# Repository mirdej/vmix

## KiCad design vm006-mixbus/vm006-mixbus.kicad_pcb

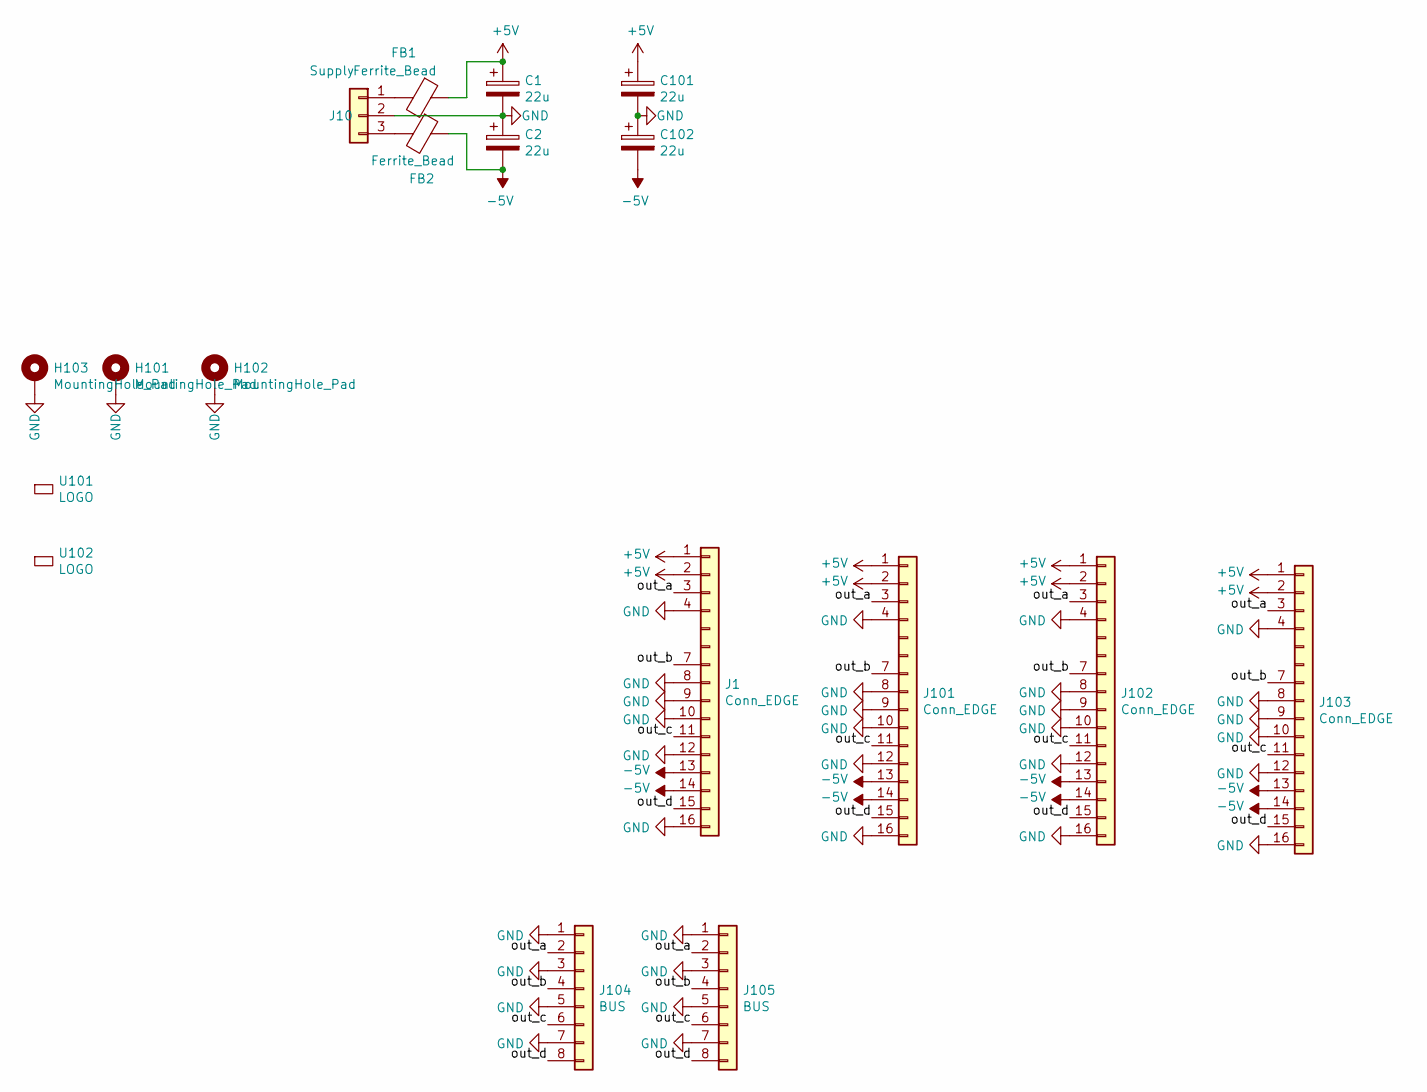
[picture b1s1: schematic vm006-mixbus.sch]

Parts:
C1, C2, C101, C102: 22u; CP_EIA-7360-38_Kemet-E_Pad2.25x4.25mm_HandSolder
FB1, FB2: Ferrite_Bead; L_1206_3216Metric_Pad1.42x1.75mm_HandSolder
H101, H102, H103: MountingHole_Pad; MountingHole_3.2mm_M3_Pad
J1, J101, J102, J103: Conn_EDGE; Samtec_MECF-08-01-L-DV-WT_2x08_P1.27mm_Polarized_Socket_Hor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
J10: Supply; Molex_KK-254_AE-6410-03A_1x03_P2.54mm_Vertical
J104, J105: BUS; PinHeader_1x08_P2.54mm_Vertical
U101: LOGO; logo_anyma
U102: LOGO; OSHW-Logo2_9.8x8mm_SilkScreen

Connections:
+5V: C1.1, C101.1, FB1.1, J1.1, J1.2, J101.1, J101.2, J102.1, J102.2, J103.1, J103.2
-5V: C2.2, C102.2, FB2.1, J1.13, J1.14, J101.13, J101.14, J102.13, J102.14, J103.13, J103.14
/out_a: J1.3, J101.3, J102.3, J103.3, J104.2, J105.2
/out_b: J1.7, J101.7, J102.7, J103.7, J104.4, J105.4
/out_c: J1.11, J101.11, J102.11, J103.11, J104.6, J105.6
/out_d: J1.15, J101.15, J102.15, J103.15, J104.8, J105.8
GND: C1.2, C2.1, C101.2, C102.1, H101.1, H102.1, H103.1, J1.4, J1.8, J1.9, J1.10, J1.12, J1.16, J10.2, J101.4, J101.8, J101.9, J101.10, J101.12, J101.16, J102.4, J102.8, J102.9, J102.10, J102.12, J102.16, J103.4, J103.8, J103.9, J103.10, J103.12, J103.16, J104.1, J104.3, J104.5, J104.7, J105.1, J105.3, J105.5, J105.7
unnamed: FB1.2, J10.1
unnamed: FB2.2, J10.3

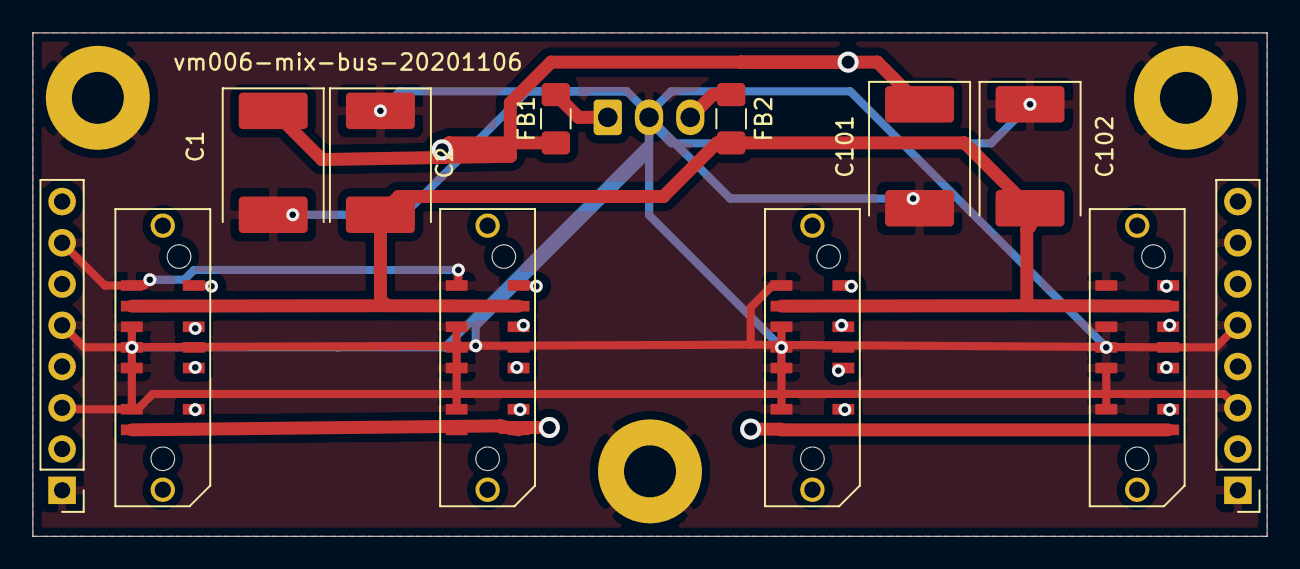
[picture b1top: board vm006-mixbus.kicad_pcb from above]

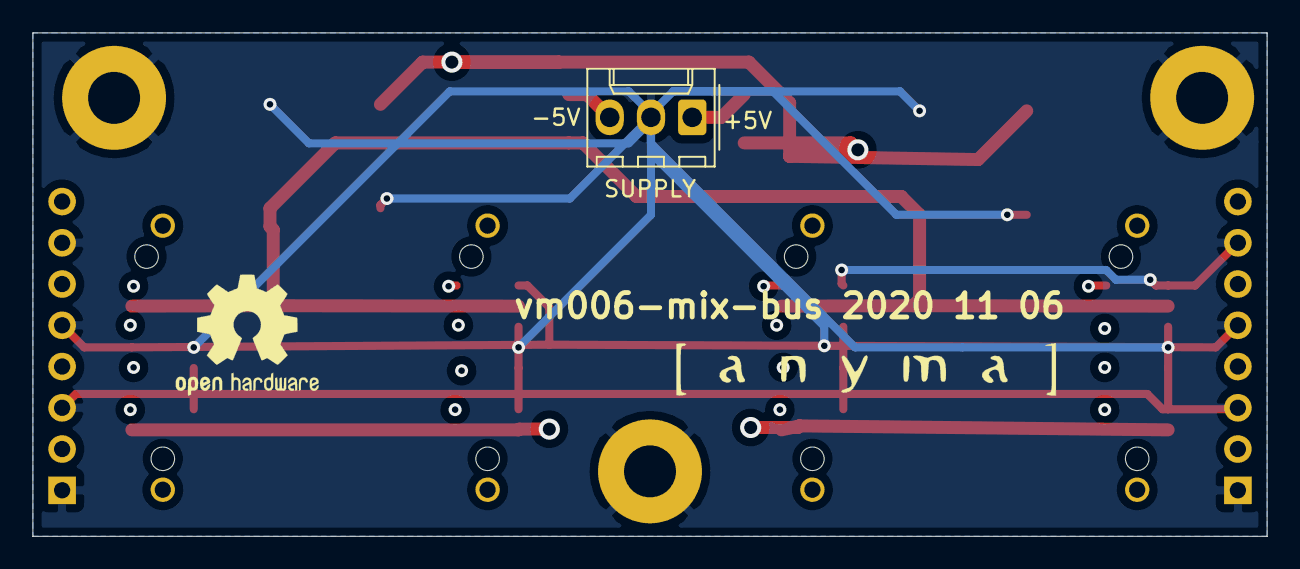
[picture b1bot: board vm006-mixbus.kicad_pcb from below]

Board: 4 copper layers, 76.0 x 31.0 mm, 18 parts (3 on the bottom side), 9 nets.

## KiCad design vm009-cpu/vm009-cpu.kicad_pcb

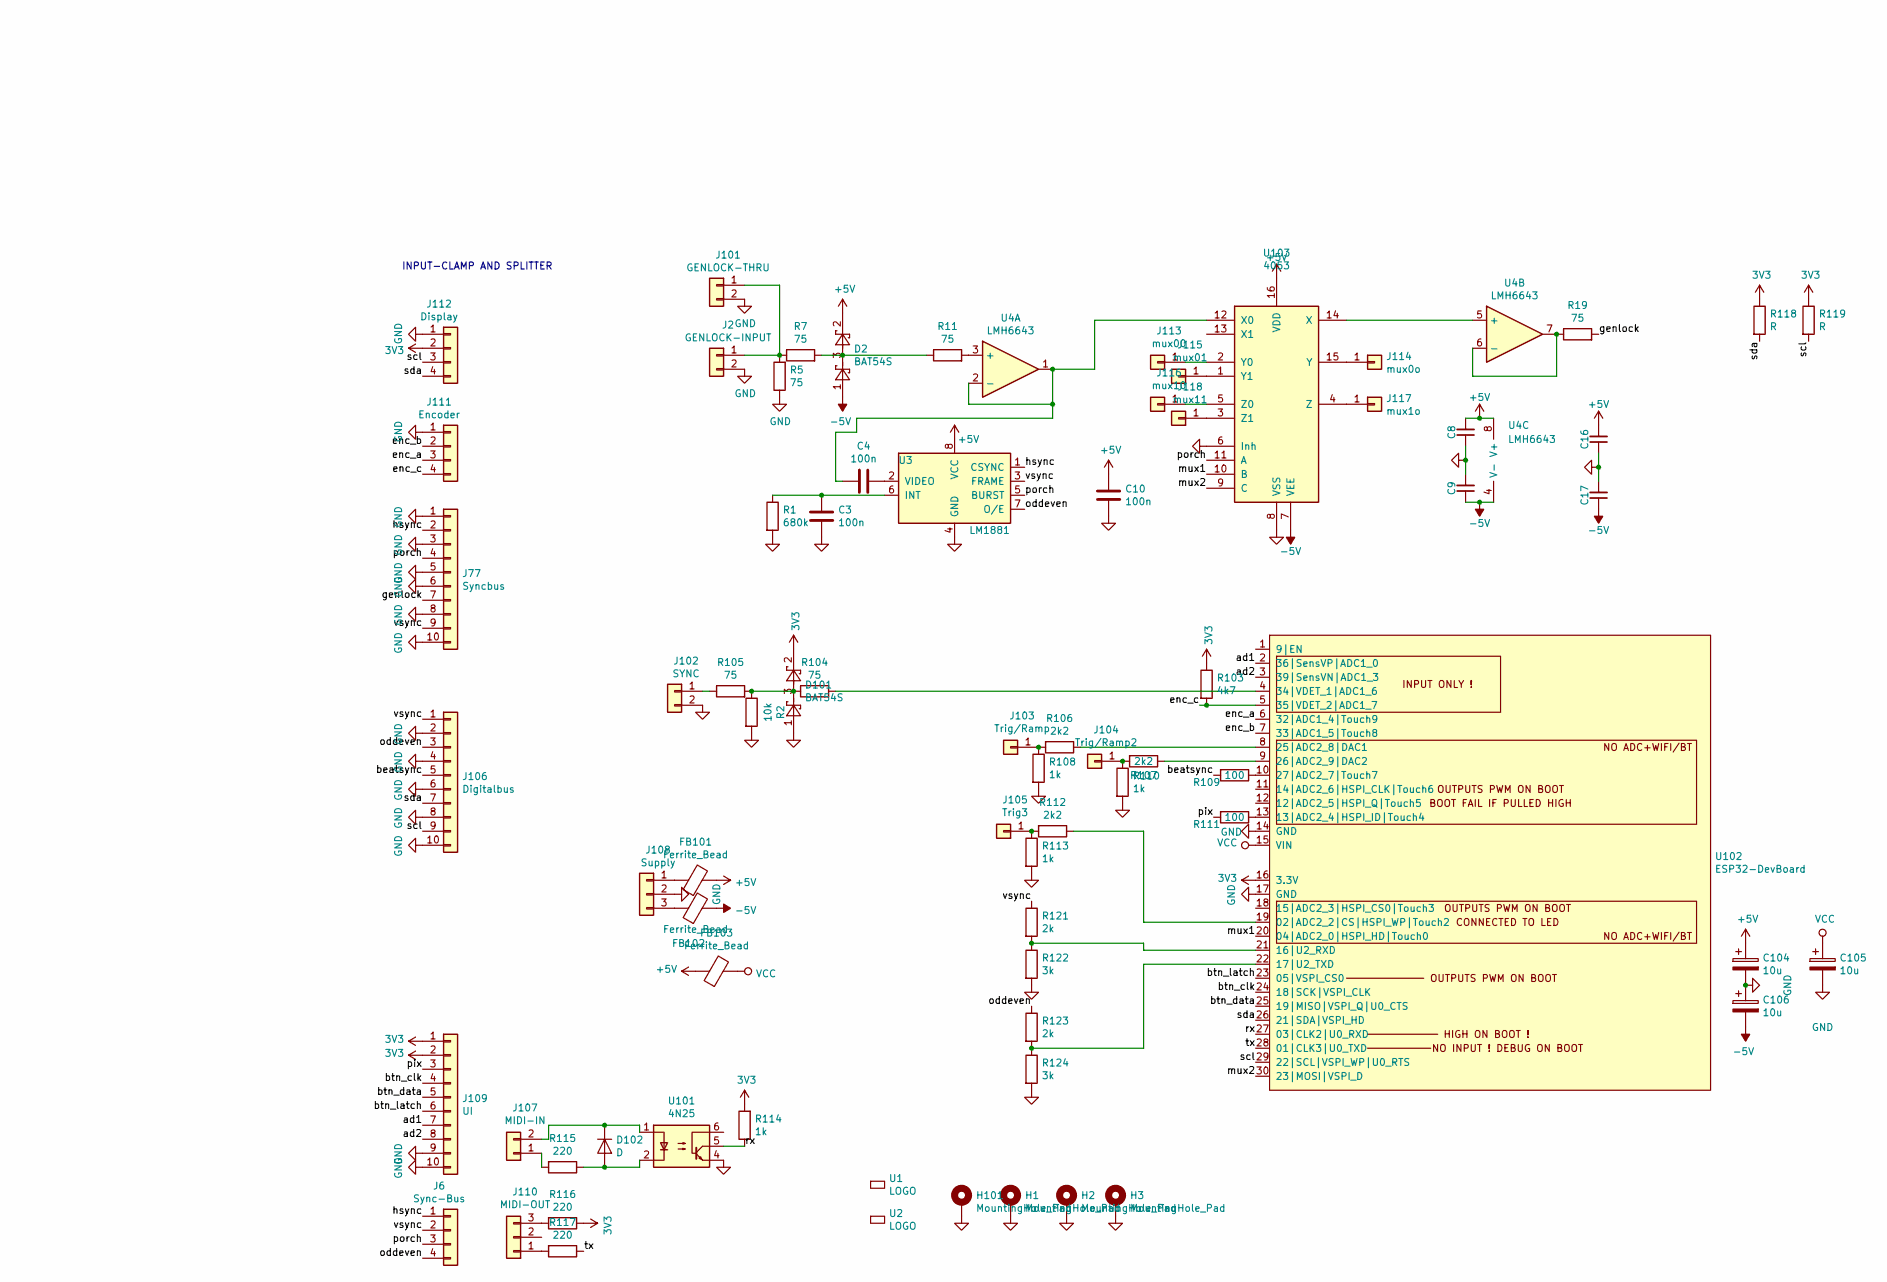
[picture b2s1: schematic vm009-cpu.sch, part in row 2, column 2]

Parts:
C3, C4, C8, C9, C10, C16, C17: 100n; C_0603_1608Metric_Pad1.05x0.95mm_HandSolder
C104, C105, C106: 10u; CP_EIA-3528-21_Kemet-B_Pad1.50x2.35mm_HandSolder
D2, D101: BAT54S; SOT-23
D102: D; D_MiniMELF_Handsoldering
FB101, FB102, FB103: Ferrite_Bead; L_0805_2012Metric_Pad1.15x1.40mm_HandSolder
H1, H2, H3, H101: MountingHole_Pad; MountingHole_2.7mm_M2.5_ISO7380_Pad
J2: GENLOCK-INPUT; Molex_KK-254_AE-6410-02A_1x02_P2.54mm_Vertical
J6: Sync-Bus; Molex_KK-254_AE-6410-04A_1x04_P2.54mm_Vertical
J77: Syncbus; IDC-Header_2x05_P2.54mm_Vertical
J101: GENLOCK-THRU; Molex_KK-254_AE-6410-02A_1x02_P2.54mm_Vertical
J102: SYNC; Molex_KK-254_AE-6410-02A_1x02_P2.54mm_Vertical
J103: Trig/Ramp; Solderpad_1mm
J104: Trig/Ramp2; Solderpad_1mm
J105: Trig3; Solderpad_1mm
J106: Digitalbus; IDC-Header_2x05_P2.54mm_Vertical
J107: MIDI-IN; Molex_KK-254_AE-6410-02A_1x02_P2.54mm_Vertical
J108: Supply; Molex_KK-254_AE-6410-03A_1x03_P2.54mm_Vertical
J109: UI; IDC-Header_2x05_P2.54mm_Vertical
J110: MIDI-OUT; Molex_KK-254_AE-6410-03A_1x03_P2.54mm_Vertical
J111: Encoder; Molex_KK-254_AE-6410-04A_1x04_P2.54mm_Vertical
J112: Display; Molex_KK-254_AE-6410-04A_1x04_P2.54mm_Vertical
J113: mux00; Solderpad_1mm
J114: mux0o; Solderpad_1mm
J115: mux01; Solderpad_1mm
J116: mux10; Solderpad_1mm
J117: mux1o; Solderpad_1mm
J118: mux11; Solderpad_1mm
R1: 680k; R_0805_2012Metric_Pad1.15x1.40mm_HandSolder
R2: 10k; R_0805_2012Metric_Pad1.15x1.40mm_HandSolder
R5, R7, R11, R19, R104, R105: 75; R_0805_2012Metric_Pad1.15x1.40mm_HandSolder
R103: 4k7; R_0805_2012Metric_Pad1.15x1.40mm_HandSolder
R106, R107, R112: 2k2; R_0805_2012Metric_Pad1.15x1.40mm_HandSolder
R108, R110, R113, R114: 1k; R_0805_2012Metric_Pad1.15x1.40mm_HandSolder
R109, R111: 100; R_0805_2012Metric_Pad1.15x1.40mm_HandSolder
R115, R116, R117: 220; R_0805_2012Metric_Pad1.15x1.40mm_HandSolder
R118, R119: R; R_0805_2012Metric_Pad1.15x1.40mm_HandSolder
R121, R123: 2k; R_0805_2012Metric_Pad1.15x1.40mm_HandSolder
R122, R124: 3k; R_0805_2012Metric_Pad1.15x1.40mm_HandSolder
U1: LOGO; logo_anyma
U2: LOGO; OSHW-Logo2_7.3x6mm_SilkScreen
U3: LM1881; SOIC-8_3.9x4.9mm_P1.27mm
U4: LMH6643; SOIC-8_3.9x4.9mm_P1.27mm
U101: 4N25; DIP-6_W8.89mm_SMDSocket_LongPads
U102: ESP32-DevBoard; ESP32_Devboard
U103: 4053; SOIC-16_3.9x9.9mm_P1.27mm

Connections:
3V3: D101.2, J109.1, J109.2, J112.2, R103.1, R114.2, R116.1, R118.1, R119.1, U102.16 (3.3V)
+5V: C8.2, C10.1, C16.2, C104.1, D2.2, FB101.2, FB103.1, U3.8 (VCC), U4.8 (V+), U103.16 (VDD)
-5V: C9.1, C17.1, C106.2, D2.1, FB102.2, U4.4 (V-), U103.7 (VEE)
/ad1: J109.7, U102.2 (36|SensVP|ADC1_0)
/ad2: J109.8, U102.3 (39|SensVN|ADC1_3)
/beatsync: J106.5, R109.2
/btn_clk: J109.4, U102.24 (18|SCK|VSPI_CLK)
/btn_data: J109.5, U102.25 (19|MISO|VSPI_Q|U0_CTS)
/btn_latch: J109.6, U102.23 (05|VSPI_CS0)
/enc_a: J111.3, U102.6 (32|ADC1_4|Touch9)
/enc_b: J111.2, U102.7 (33|ADC1_5|Touch8)
/enc_c: J111.4, R103.2, U102.5 (35|VDET_2|ADC1_7)
/genlock: J77.7, R19.2
/hsync: J6.1, J77.2, U3.1 (CSYNC)
/mux1: U102.20 (04|ADC2_0|HSPI_HD|Touch0), U103.10 (B)
/mux2: U102.30 (23|MOSI|VSPI_D), U103.9 (C)
/oddeven: J6.4, J106.3, R123.1, U3.7 (O/E)
/pix: J109.3, R111.2
/porch: J6.3, J77.4, U3.5 (BURST), U103.11 (A)
/rx: R114.1, U101.5, U102.27 (03|CLK2|U0_RXD)
/scl: J106.9, J112.3, R119.2, U102.29 (22|SCL|VSPI_WP|U0_RTS)
/sda: J106.7, J112.4, R118.2, U102.26 (21|SDA|VSPI_HD)
/tx: R117.1, U102.28 (01|CLK3|U0_TXD)
/vsync: J6.2, J77.9, J106.1, R121.1, U3.3 (FRAME)
GND: C3.2, C8.1, C9.2, C10.2, C16.1, C17.2, C104.2, C105.2, C106.1, D101.1, H1.1, H2.1, H3.1, H101.1, J2.2, J77.1, J77.3, J77.5, J77.6, J77.8, J77.10, J101.2, J102.2, J106.2, J106.4, J106.6, J106.8, J106.10, J108.2, J109.9, J109.10, J111.1, J112.1, R1.2, R2.2, R5.1, R108.2, R110.2, R113.2, R122.2, R124.2, U3.4 (GND), U101.4, U102.14 (GND), U102.17 (GND), U103.6 (Inh), U103.8 (VSS)
unnamed: C3.1, R1.1, U3.6 (INT)
unnamed: C4.1, U3.2 (VIDEO)
unnamed: C4.2, U4.1, U4.2 (-), U103.12 (X0)
unnamed: D2.3, R7.2, R11.1
unnamed: D101.3, R2.1, R104.1, R105.2
unnamed: D102.1 (K), J107.2, U101.1
unnamed: D102.2 (A), R115.1, U101.2
unnamed: FB101.1, J108.1
unnamed: FB102.1, J108.3
unnamed: J2.1, J101.1, R5.2, R7.1
unnamed: J102.1, R105.1
unnamed: J103.1, R106.2, R108.1
unnamed: J104.1, R107.2, R110.1
unnamed: J105.1, R112.2, R113.1
unnamed: J107.1, R115.2
unnamed: J110.1, R117.2
unnamed: J110.3, R116.2
unnamed: J113.1, U103.2 (Y0)
unnamed: J114.1, U103.15 (Y)
unnamed: J115.1, U103.1 (Y1)
unnamed: J116.1, U103.5 (Z0)
unnamed: J117.1, U103.4 (Z)
unnamed: J118.1, U103.3 (Z1)
unnamed: R11.2, U4.3 (+)
unnamed: R19.1, U4.6 (-), U4.7
unnamed: R104.2, U102.4 (34|VDET_1|ADC1_6)
unnamed: R106.1, U102.8 (25|ADC2_8|DAC1)
unnamed: R107.1, U102.9 (26|ADC2_9|DAC2)
unnamed: R109.1, U102.10 (27|ADC2_7|Touch7)
unnamed: R111.1, U102.13 (13|ADC2_4|HSPI_ID|Touch4)
unnamed: R112.1, U102.19 (02|ADC2_2|CS|HSPI_WP|Touch2)
unnamed: R121.2, R122.1, U102.21 (16|U2_RXD)
unnamed: R123.2, R124.1, U102.22 (17|U2_TXD)
unnamed: U4.5 (+), U103.14 (X)
VCC: C105.1, FB103.2, U102.15 (VIN)

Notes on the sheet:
INPUT-CLAMP AND SPLITTER

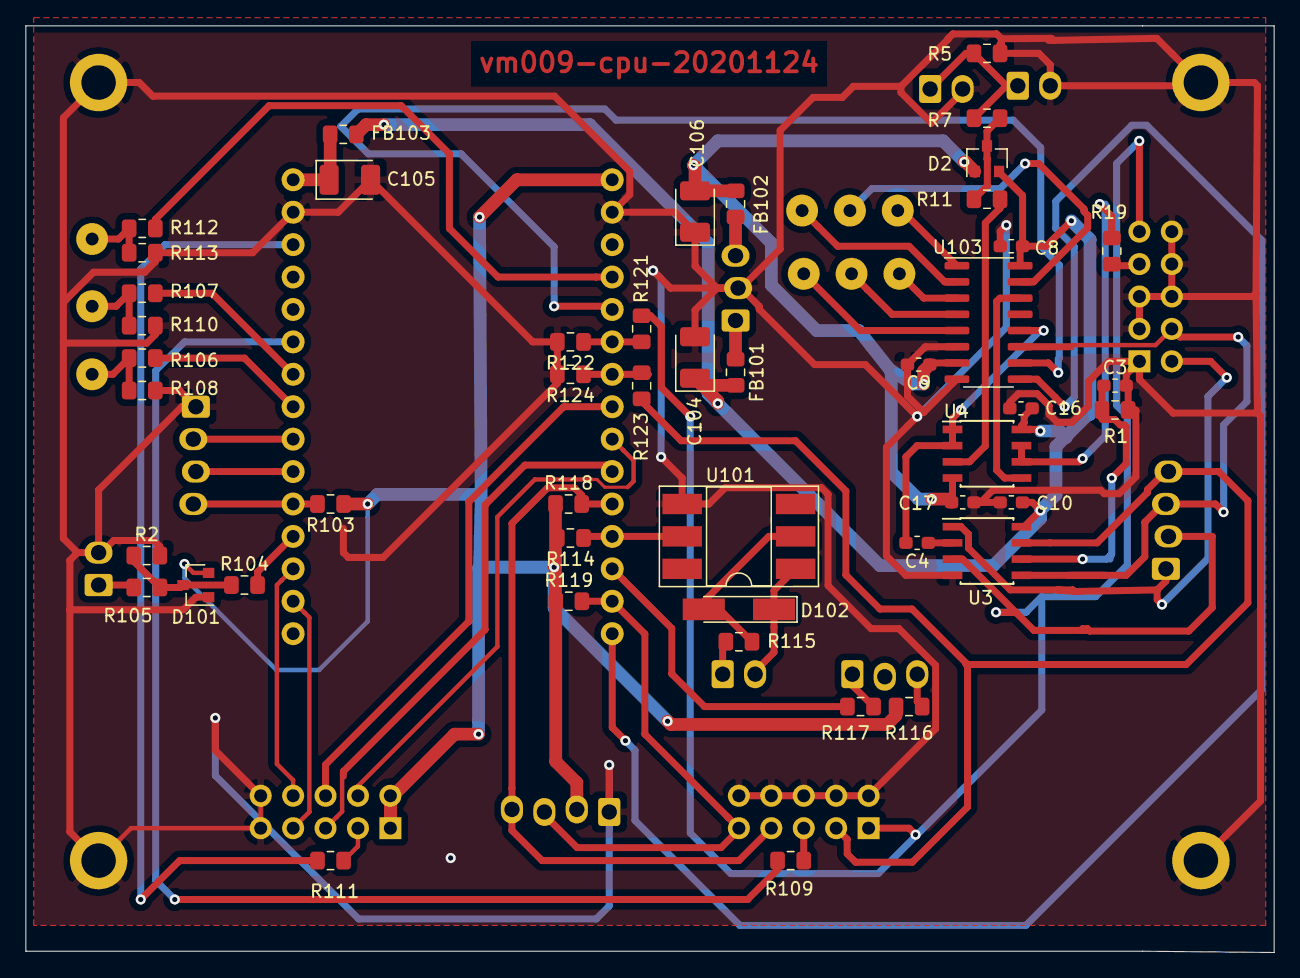
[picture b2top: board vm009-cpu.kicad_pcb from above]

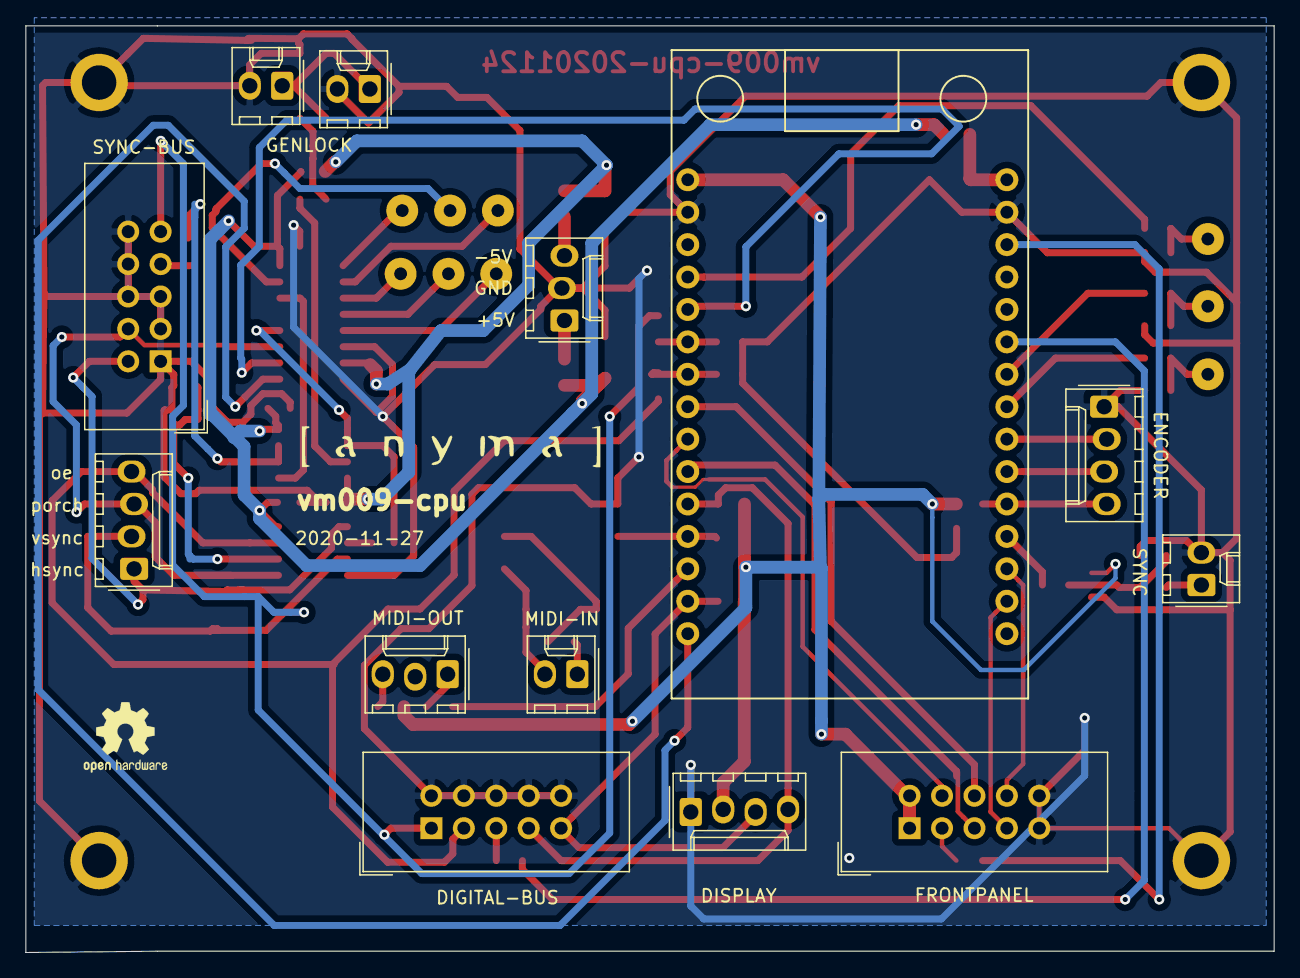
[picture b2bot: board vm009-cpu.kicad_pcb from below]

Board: 2 copper layers, 97.8 x 72.6 mm, 75 parts (15 on the bottom side), 60 nets.

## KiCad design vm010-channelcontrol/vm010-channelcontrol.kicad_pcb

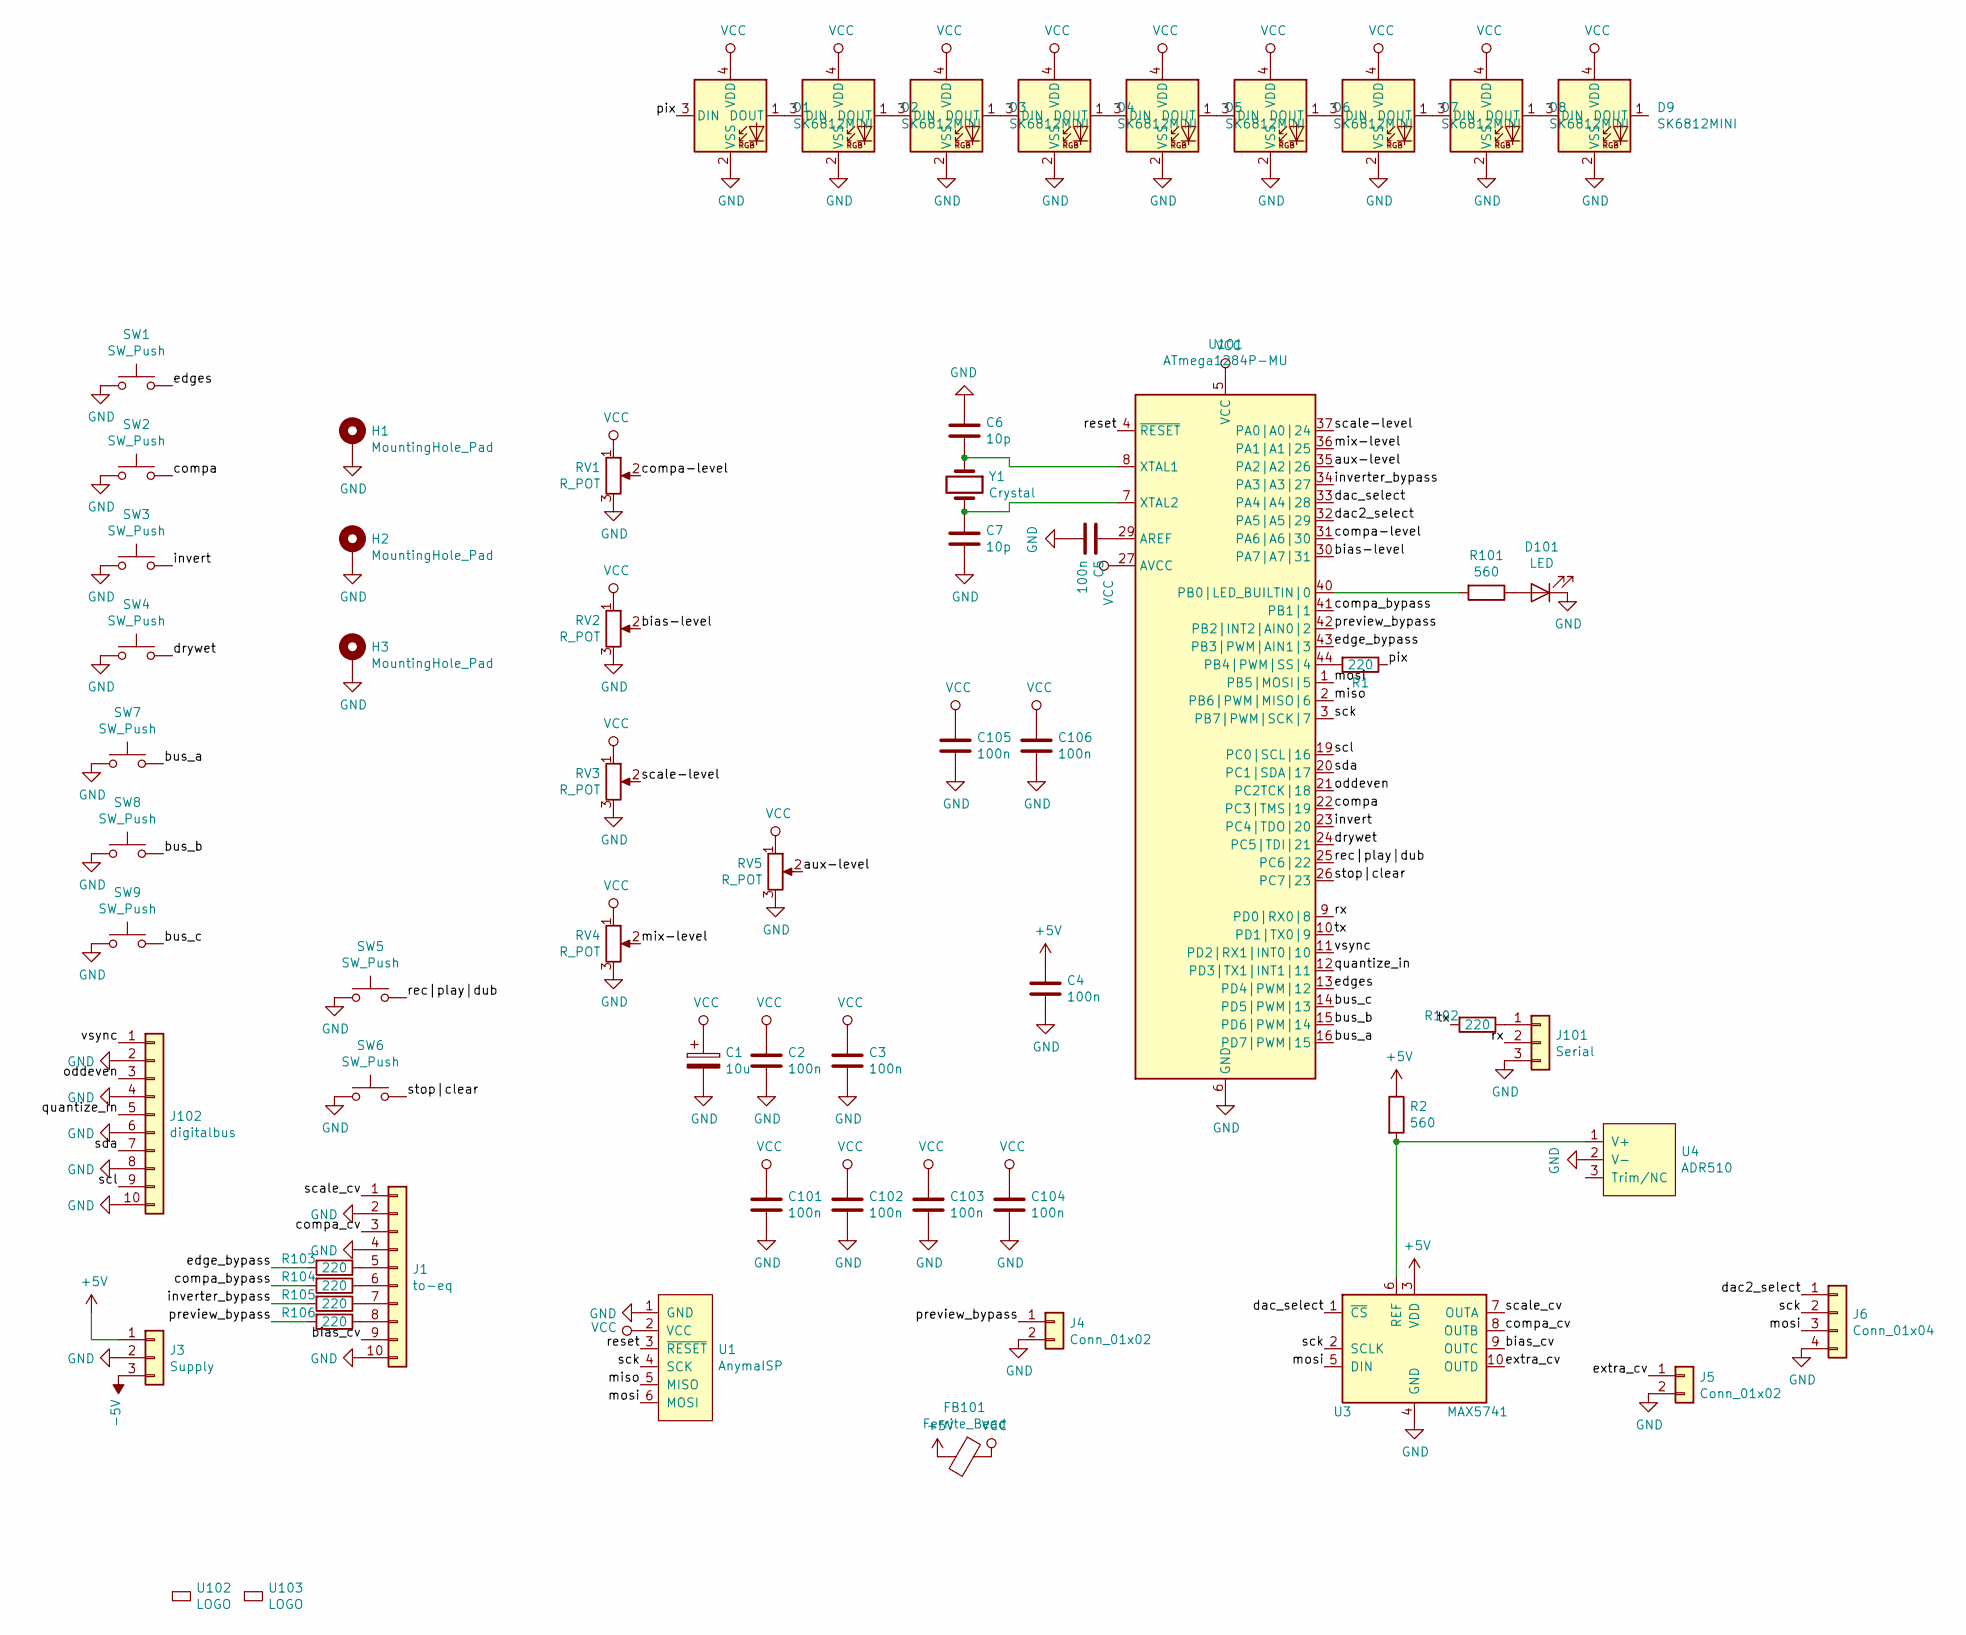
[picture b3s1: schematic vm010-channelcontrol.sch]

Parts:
C1: 10u; CP_EIA-3528-21_Kemet-B_Pad1.50x2.35mm_HandSolder
C2, C3, C4, C5, C101, C102, C103, C104, C105, C106: 100n; R_0603_1608Metric_Pad1.05x0.95mm_HandSolder
C6, C7: 10p; R_0805_2012Metric_Pad1.15x1.40mm_HandSolder
D1, D2, D3, D4, D5, D6, D7, D8, D9: SK6812MINI; LED_SK6812MINI_PLCC4_3.5x3.5mm_P1.75mm
D101: LED; LED_0805_2012Metric
FB101: Ferrite_Bead; L_0805_2012Metric_Pad1.15x1.40mm_HandSolder
H1, H2, H3: MountingHole_Pad; MountingHole_2.2mm_M2_DIN965_Pad
J1: to-eq; IDC-Header_2x05_P2.54mm_Vertical
J3: Supply; Molex_KK-254_AE-6410-03A_1x03_P2.54mm_Vertical
J4, J5: Conn_01x02; Molex_KK-254_AE-6410-02A_1x02_P2.54mm_Vertical
J6: Conn_01x04; Molex_KK-254_AE-6410-04A_1x04_P2.54mm_Vertical
J101: Serial; Molex_KK-254_AE-6410-03A_1x03_P2.54mm_Vertical
J102: digitalbus; IDC-Header_2x05_P2.54mm_Vertical
R1, R102, R103, R104, R105, R106: 220; R_0805_2012Metric_Pad1.15x1.40mm_HandSolder
R2, R101: 560; R_0805_2012Metric_Pad1.15x1.40mm_HandSolder
RV1, RV2, RV3, RV5: R_POT; Potentiometer_Alps_RK09K_Single_Vertical
RV4: R_POT; Potentiometer_Alps_RS6011xP_Slide
SW1, SW2, SW3, SW4, SW5, SW6, SW7, SW8, SW9: SW_Push; Alps_Tactile_Switch
U1: AnymaISP; PinHeader_1x06_P2.54mm_Vertical
U3: MAX5741; MSOP-10_3x3mm_P0.5mm
U4: ADR510; SOT-23
U101: ATmega1284P-MU; QFN-44-1EP_7x7mm_P0.5mm_EP5.2x5.2mm
U102: LOGO; logo_anyma
U103: LOGO; OSHW-Logo2_7.3x6mm_SilkScreen
Y1: Crystal; Crystal_SMD_HC49-SD

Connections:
+5V: C4.1, FB101.2, J3.1, R2.1, U3.3 (VDD)
/aux-level: RV5.2, U101.35 (PA2|A2|26)
/bias-level: RV2.2, U101.30 (PA7|A7|31)
/bias_cv: J1.9, U3.9 (OUTC)
/bus_a: SW7.2, U101.16 (PD7|PWM|15)
/bus_b: SW8.2, U101.15 (PD6|PWM|14)
/bus_c: SW9.2, U101.14 (PD5|PWM|13)
/compa: SW2.2, U101.22 (PC3|TMS|19)
/compa-level: RV1.2, U101.31 (PA6|A6|30)
/compa_bypass: R104.2, U101.41 (PB1|1)
/compa_cv: J1.3, U3.8 (OUTB)
/dac2_select: J6.1, U101.32 (PA5|A5|29)
/dac_select: U3.1 (~CS~), U101.33 (PA4|A4|28)
/drywet: SW4.2, U101.24 (PC5|TDI|21)
/edge_bypass: R103.2, U101.43 (PB3|PWM|AIN1|3)
/edges: SW1.2, U101.13 (PD4|PWM|12)
/extra_cv: J5.1, U3.10 (OUTD)
/invert: SW3.2, U101.23 (PC4|TDO|20)
/inverter_bypass: R105.2, U101.34 (PA3|A3|27)
/miso: U1.5 (MISO), U101.2 (PB6|PWM|MISO|6)
/mix-level: RV4.2, U101.36 (PA1|A1|25)
/mosi: J6.3, U1.6 (MOSI), U3.5 (DIN), U101.1 (PB5|MOSI|5)
/oddeven: J102.3, U101.21 (PC2TCK|18)
/pix: D1.3 (DIN), R1.1
/preview_bypass: J4.1, R106.2, U101.42 (PB2|INT2|AIN0|2)
/quantize_in: J102.5, U101.12 (PD3|TX1|INT1|11)
/rec|play|dub: SW5.2, U101.25 (PC6|22)
/reset: U1.3 (~RESET), U101.4 (~RESET)
/rx: J101.2, U101.9 (PD0|RX0|8)
/scale-level: RV3.2, U101.37 (PA0|A0|24)
/scale_cv: J1.1, U3.7 (OUTA)
/sck: J6.2, U1.4 (SCK), U3.2 (SCLK), U101.3 (PB7|PWM|SCK|7)
/scl: J102.9, U101.19 (PC0|SCL|16)
/sda: J102.7, U101.20 (PC1|SDA|17)
/stop|clear: SW6.2, U101.26 (PC7|23)
/tx: R102.2, U101.10 (PD1|TX0|9)
/vsync: J102.1, U101.11 (PD2|RX1|INT0|10)
GND: C1.2, C2.2, C3.2, C4.2, C5.2, C6.1, C7.2, C101.2, C102.2, C103.2, C104.2, C105.2, C106.2, D1.2 (VSS), D2.2 (VSS), D3.2 (VSS), D4.2 (VSS), D5.2 (VSS), D6.2 (VSS), D7.2 (VSS), D8.2 (VSS), D9.2 (VSS), D101.1 (K), H1.1, H2.1, H3.1, J1.2, J1.4, J1.10, J3.2, J4.2, J5.2, J6.4, J101.3, J102.2, J102.4, J102.6, J102.8, J102.10, RV1.3, RV2.3, RV3.3, RV4.3, RV5.3, SW1.1, SW2.1, SW3.1, SW4.1, SW5.1, SW6.1, SW7.1, SW8.1, SW9.1, U1.1 (GND), U3.4 (GND), U4.2 (V-), U101.6 (GND), U101.18 (GND), U101.28 (GND), U101.39 (GND), U101.45 (GND); also elsewhere on the board
unnamed: C5.1, U101.29 (AREF)
unnamed: C6.2, U101.8 (XTAL1), Y1.1
unnamed: C7.1, U101.7 (XTAL2), Y1.2
unnamed: D1.1 (DOUT), D2.3 (DIN)
unnamed: D2.1 (DOUT), D3.3 (DIN)
unnamed: D3.1 (DOUT), D4.3 (DIN)
unnamed: D4.1 (DOUT), D5.3 (DIN)
unnamed: D5.1 (DOUT), D6.3 (DIN)
unnamed: D6.1 (DOUT), D7.3 (DIN)
unnamed: D7.1 (DOUT), D8.3 (DIN)
unnamed: D8.1 (DOUT), D9.3 (DIN)
unnamed: D101.2 (A), R101.1
unnamed: J1.5, R103.1
unnamed: J1.6, R104.1
unnamed: J1.7, R105.1
unnamed: J1.8, R106.1
unnamed: J101.1, R102.1
unnamed: R1.2, U101.44 (PB4|PWM|SS|4)
unnamed: R2.2, U3.6 (REF), U4.1 (V+)
unnamed: R101.2, U101.40 (PB0|LED_BUILTIN|0)
VCC: C1.1, C2.1, C3.1, C101.1, C102.1, C103.1, C104.1, C105.1, C106.1, D1.4 (VDD), D2.4 (VDD), D3.4 (VDD), D4.4 (VDD), D5.4 (VDD), D6.4 (VDD), D7.4 (VDD), D8.4 (VDD), D9.4 (VDD), FB101.1, RV1.1, RV2.1, RV3.1, RV4.1, RV5.1, U1.2 (VCC), U101.5 (VCC), U101.17 (VCC), U101.27 (AVCC), U101.38 (VCC)

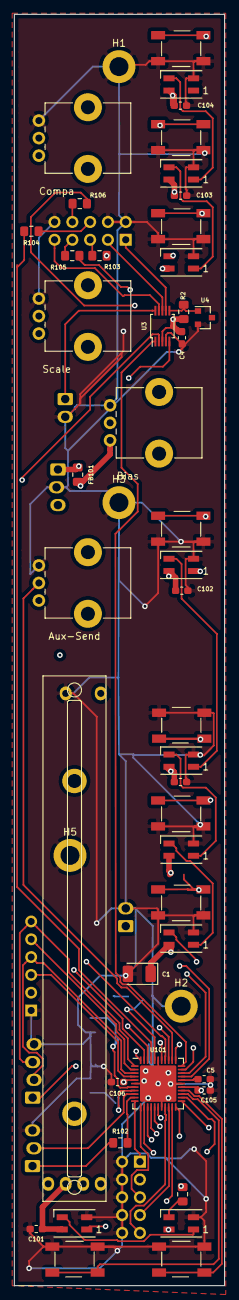
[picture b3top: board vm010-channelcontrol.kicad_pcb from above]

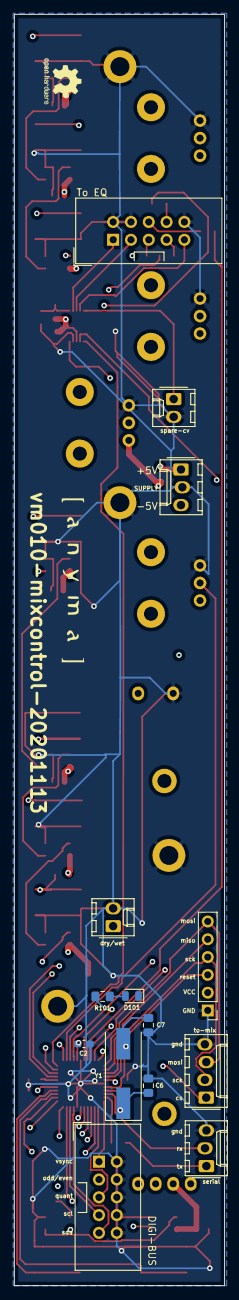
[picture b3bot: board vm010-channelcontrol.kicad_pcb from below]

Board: 4 copper layers, 30.0 x 181.4 mm, 64 parts (16 on the bottom side), 59 nets.

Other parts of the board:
H5: MountingHole_Pad; MountingHole_2.7mm_M2.5_DIN965_Pad

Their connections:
GND: H5.1; also elsewhere on the board

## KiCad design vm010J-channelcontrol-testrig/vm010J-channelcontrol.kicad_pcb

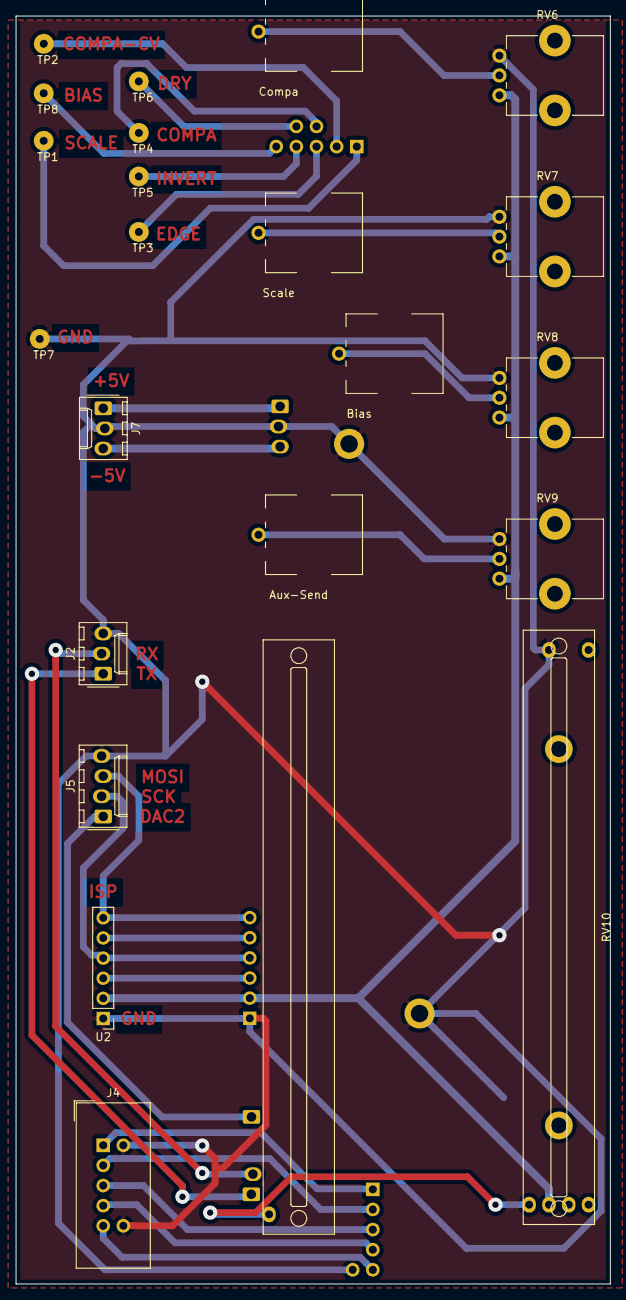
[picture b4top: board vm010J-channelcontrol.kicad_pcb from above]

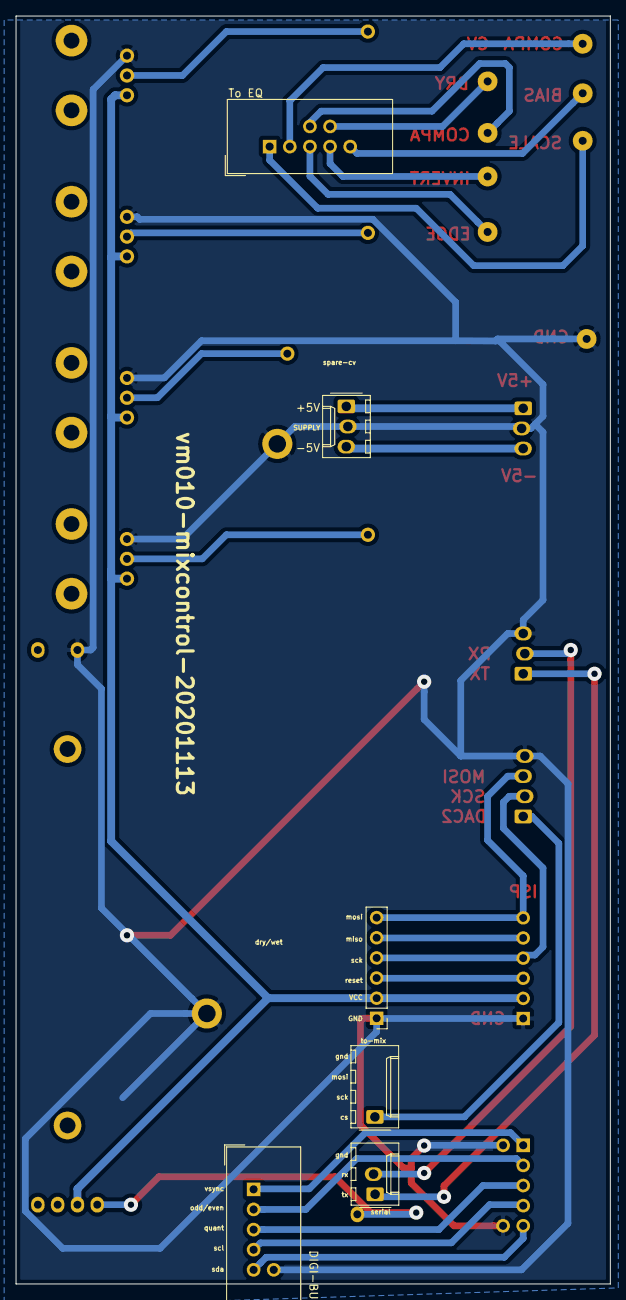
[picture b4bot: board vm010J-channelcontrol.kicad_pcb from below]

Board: 4 copper layers, 75.0 x 160.0 mm, 31 parts (6 on the bottom side), 28 nets.

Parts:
H2, H3: MountingHole_Pad; MountingHole_2.2mm_M2_DIN965_Pad
J1: to-eq; IDC-Header_2x05_P2.54mm_Vertical
J2, J101: Serial; Molex_KK-254_AE-6410-03A_1x03_P2.54mm_Vertical
J3, J7: Supply; Molex_KK-254_AE-6410-03A_1x03_P2.54mm_Vertical
J4, J102: digitalbus; IDC-Header_2x05_P2.54mm_Vertical
J5, J6: Conn_01x04; Molex_KK-254_AE-6410-04A_1x04_P2.54mm_Vertical
RV1, RV2, RV3, RV5, RV6, RV7, RV8, RV9: R_POT; Potentiometer_Alps_RK09K_Single_Vertical
RV4, RV10: R_POT; Potentiometer_Alps_RS6011xP_Slide
TP1, TP2, TP3, TP4, TP5, TP6, TP7, TP8: TestPoint; Solderpad_1mm
U1, U2: AnymaISP; PinHeader_1x06_P2.54mm_Vertical

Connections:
+5V: J3.1, J7.1
-5V: J3.3, J7.3
/aux-level: RV5.2, RV9.2
/bias-level: RV2.2, RV7.2
/bias_cv: J1.9, TP8.1
/compa-level: RV1.2, RV6.2
/compa_bypass: J1.6, TP4.1
/compa_cv: J1.3, TP2.1
/dac2_select: J5.1, J6.1
/edge_bypass: J1.5, TP3.1
/inverter_bypass: J1.7, TP5.1
/miso: U1.5, U2.5
/mix-level: RV4.2, RV10.2
/mosi: J5.3, U1.6, U2.6
/oddeven: J4.3, J102.3
/preview_bypass: J1.8, TP6.1
/quantize_in: J4.5, J102.5
/reset: U1.3, U2.3
/rx: J2.2, J101.2
/scale-level: RV3.2, RV8.2
/scale_cv: J1.1, TP1.1
/sck: J5.2, U1.4, U2.4
/scl: J4.9, J102.9
/sda: J4.7, J102.7
/tx: J2.1, J101.1
/vsync: J4.1, J102.1
GND: H2.1, H3.1, J2.3, J3.2, J4.2, J4.10, J5.4, J7.2, J102.10, RV6.3, RV7.3, RV8.3, RV9.3, RV10.3, TP7.1, U1.1, U2.1
VCC: RV6.1, RV7.1, RV8.1, RV9.1, RV10.1, U1.2, U2.2

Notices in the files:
parts and their libraries:
Copyright 2016 Accelerated Designs. All rights reserved.
